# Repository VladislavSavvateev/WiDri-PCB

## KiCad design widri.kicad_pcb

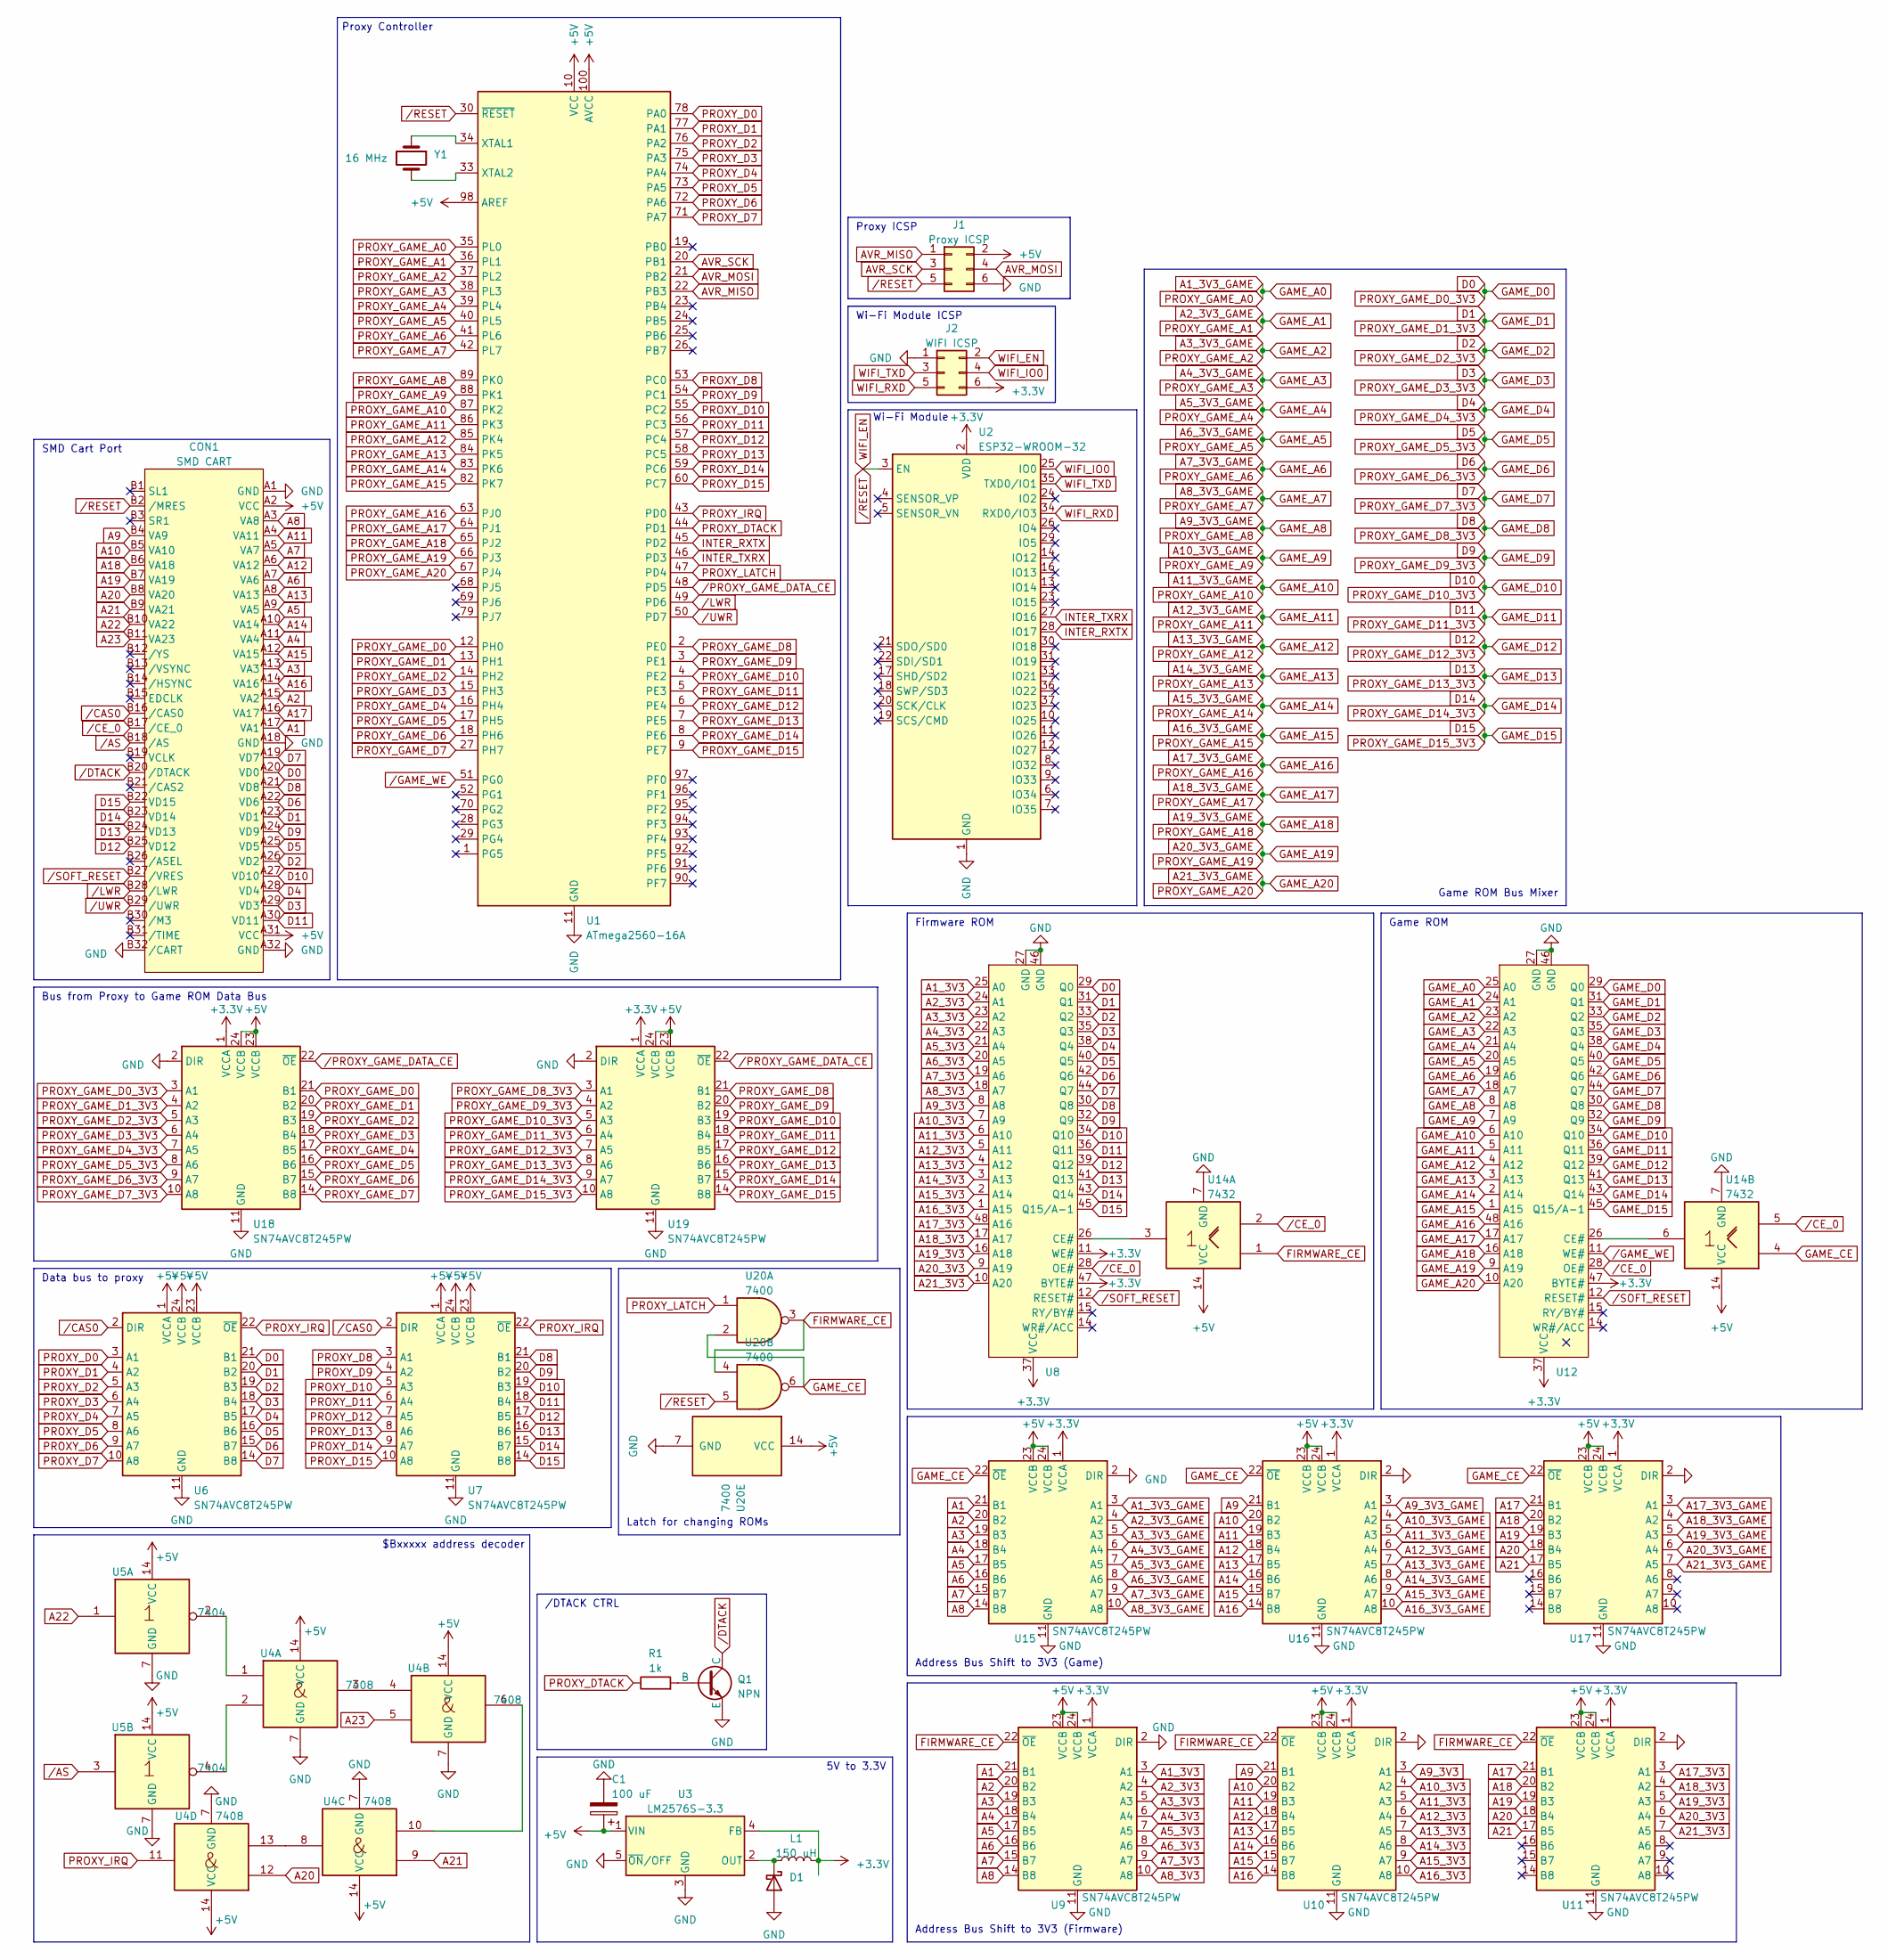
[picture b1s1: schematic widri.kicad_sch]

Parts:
C1: 100 uF; CP_Elec_6.3x5.4
CON1: SMD CART; SMD cart edge connector
D1: D_SMA
J1: Proxy ICSP; PinHeader_2x03_P2.54mm_Vertical
J2: WIFI ICSP; PinHeader_2x03_P2.54mm_Vertical
L1: 150 uH; L_1812_4532Metric
Q1: NPN; TSOP-6_1.65x3.05mm_P0.95mm
R1: 1k; R_1206_3216Metric
U1: ATmega2560-16A; TQFP-100_14x14mm_P0.5mm
U2: ESP32-WROOM-32
U3: LM2576S-3.3; TO-263-5_TabPin3
U4: 7408; SOIC-14_3.9x8.7mm_P1.27mm
U5: 7404; SOIC-14_3.9x8.7mm_P1.27mm
U6, U7, U9, U10, U11, U15, U16, U17, U18, U19: SN74AVC8T245PW; TSSOP-24_4.4x7.8mm_P0.65mm
U8, U12: TSOP-I-48_18.4x12mm_P0.5mm
U14: 7432; SOIC-14_3.9x8.7mm_P1.27mm
U20: 7400; SOIC-14_3.9x8.7mm_P1.27mm
Y1: 16 MHz; Crystal_HC49-U_Vertical

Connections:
+3.3V: J2.6, L1.2, U2.2 (VDD), U3.4 (FB), U8.11 (WE#), U8.37 (VCC), U8.47 (BYTE#), U9.1 (VCCA), U10.1 (VCCA), U11.1 (VCCA), U12.37 (VCC), U12.47 (BYTE#), U15.1 (VCCA), U16.1 (VCCA), U17.1 (VCCA), U18.1 (VCCA), U19.1 (VCCA)
+5V: C1.1, CON1.A2 (VCC), CON1.A31 (VCC), J1.2, U1.10 (VCC), U1.31 (VCC), U1.61 (VCC), U1.80 (VCC), U1.98 (AREF), U1.100 (AVCC), U3.1 (VIN), U4.14 (VCC), U5.14 (VCC), U6.1 (VCCA), U6.23 (VCCB), U6.24 (VCCB), U7.1 (VCCA), U7.23 (VCCB), U7.24 (VCCB), U9.23 (VCCB), U9.24 (VCCB), U10.23 (VCCB), U10.24 (VCCB), U11.23 (VCCB), U11.24 (VCCB), U14.14 (VCC), U15.23 (VCCB), U15.24 (VCCB), U16.23 (VCCB), U16.24 (VCCB), U17.23 (VCCB), U17.24 (VCCB), U18.23 (VCCB), U18.24 (VCCB), U19.23 (VCCB), U19.24 (VCCB), U20.14 (VCC)
A1: CON1.A17 (VA1), U9.21 (B1), U15.21 (B1)
A1_3V3: U8.25 (A0), U9.3 (A1)
A1_3V3_GAME: U1.35 (PL0), U12.25 (A0), U15.3 (A1)
A2: CON1.A15 (VA2), U9.20 (B2), U15.20 (B2)
A2_3V3: U8.24 (A1), U9.4 (A2)
A2_3V3_GAME: U1.36 (PL1), U12.24 (A1), U15.4 (A2)
A3: CON1.A13 (VA3), U9.19 (B3), U15.19 (B3)
A3_3V3: U8.23 (A2), U9.5 (A3)
A3_3V3_GAME: U1.37 (PL2), U12.23 (A2), U15.5 (A3)
A4: CON1.A11 (VA4), U9.18 (B4), U15.18 (B4)
A4_3V3: U8.22 (A3), U9.6 (A4)
A4_3V3_GAME: U1.38 (PL3), U12.22 (A3), U15.6 (A4)
A5: CON1.A9 (VA5), U9.17 (B5), U15.17 (B5)
A5_3V3: U8.21 (A4), U9.7 (A5)
A5_3V3_GAME: U1.39 (PL4), U12.21 (A4), U15.7 (A5)
A6: CON1.A7 (VA6), U9.16 (B6), U15.16 (B6)
A6_3V3: U8.20 (A5), U9.8 (A6)
A6_3V3_GAME: U1.40 (PL5), U12.20 (A5), U15.8 (A6)
A7: CON1.A5 (VA7), U9.15 (B7), U15.15 (B7)
A7_3V3: U8.19 (A6), U9.9 (A7)
A7_3V3_GAME: U1.41 (PL6), U12.19 (A6), U15.9 (A7)
A8: CON1.A3 (VA8), U9.14 (B8), U15.14 (B8)
A8_3V3: U8.18 (A7), U9.10 (A8)
A8_3V3_GAME: U1.42 (PL7), U12.18 (A7), U15.10 (A8)
A9: CON1.B4 (VA9), U10.21 (B1), U16.21 (B1)
A9_3V3: U8.8 (A8), U10.3 (A1)
A9_3V3_GAME: U1.89 (PK0), U12.8 (A8), U16.3 (A1)
A10: CON1.B5 (VA10), U10.20 (B2), U16.20 (B2)
A10_3V3: U8.7 (A9), U10.4 (A2)
A10_3V3_GAME: U1.88 (PK1), U12.7 (A9), U16.4 (A2)
A11: CON1.A4 (VA11), U10.19 (B3), U16.19 (B3)
A11_3V3: U8.6 (A10), U10.5 (A3)
A11_3V3_GAME: U1.87 (PK2), U12.6 (A10), U16.5 (A3)
A12: CON1.A6 (VA12), U10.18 (B4), U16.18 (B4)
A12_3V3: U8.5 (A11), U10.6 (A4)
A12_3V3_GAME: U1.86 (PK3), U12.5 (A11), U16.6 (A4)
A13: CON1.A8 (VA13), U10.17 (B5), U16.17 (B5)
A13_3V3: U8.4 (A12), U10.7 (A5)
A13_3V3_GAME: U1.85 (PK4), U12.4 (A12), U16.7 (A5)
A14: CON1.A10 (VA14), U10.16 (B6), U16.16 (B6)
A14_3V3: U8.3 (A13), U10.8 (A6)
A14_3V3_GAME: U1.84 (PK5), U12.3 (A13), U16.8 (A6)
A15: CON1.A12 (VA15), U10.15 (B7), U16.15 (B7)
A15_3V3: U8.2 (A14), U10.9 (A7)
A15_3V3_GAME: U1.83 (PK6), U12.2 (A14), U16.9 (A7)
A16: CON1.A14 (VA16), U10.14 (B8), U16.14 (B8)
A16_3V3: U8.1 (A15), U10.10 (A8)
A16_3V3_GAME: U1.82 (PK7), U12.1 (A15), U16.10 (A8)
A17: CON1.A16 (VA17), U11.21 (B1), U17.21 (B1)
A17_3V3: U8.48 (A16), U11.3 (A1)
A17_3V3_GAME: U1.63 (PJ0), U12.48 (A16), U17.3 (A1)
A18: CON1.B6 (VA18), U11.20 (B2), U17.20 (B2)
A18_3V3: U8.17 (A17), U11.4 (A2)
A18_3V3_GAME: U1.64 (PJ1), U12.17 (A17), U17.4 (A2)
A19: CON1.B7 (VA19), U11.19 (B3), U17.19 (B3)
A19_3V3: U8.16 (A18), U11.5 (A3)
A19_3V3_GAME: U1.65 (PJ2), U12.16 (A18), U17.5 (A3)
A20: CON1.B8 (VA20), U4.12, U11.18 (B4), U17.18 (B4)
A20_3V3: U8.9 (A19), U11.6 (A4)
A20_3V3_GAME: U1.66 (PJ3), U12.9 (A19), U17.6 (A4)
A21: CON1.B9 (VA21), U4.9, U11.17 (B5), U17.17 (B5)
A21_3V3: U8.10 (A20), U11.7 (A5)
A21_3V3_GAME: U1.67 (PJ4), U12.10 (A20), U17.7 (A5)
A22: CON1.B10 (VA22), U5.1
A23: CON1.B11 (VA23), U4.5
AVR_MISO: J1.1, U1.22 (PB3)
AVR_MOSI: J1.4, U1.21 (PB2)
AVR_SCK: J1.3, U1.20 (PB1)
D0: CON1.A20 (VD0), U6.21 (B1), U8.29 (Q0), U12.29 (Q0), U18.3 (A1)
D1: CON1.A23 (VD1), U6.20 (B2), U8.31 (Q1), U12.31 (Q1), U18.4 (A2)
D2: CON1.A26 (VD2), U6.19 (B3), U8.33 (Q2), U12.33 (Q2), U18.5 (A3)
D3: CON1.A29 (VD3), U6.18 (B4), U8.35 (Q3), U12.35 (Q3), U18.6 (A4)
D4: CON1.A28 (VD4), U6.17 (B5), U8.38 (Q4), U12.38 (Q4), U18.7 (A5)
D5: CON1.A25 (VD5), U6.16 (B6), U8.40 (Q5), U12.40 (Q5), U18.8 (A6)
D6: CON1.A22 (VD6), U6.15 (B7), U8.42 (Q6), U12.42 (Q6), U18.9 (A7)
D7: CON1.A19 (VD7), U6.14 (B8), U8.44 (Q7), U12.44 (Q7), U18.10 (A8)
D8: CON1.A21 (VD8), U7.21 (B1), U8.30 (Q8), U12.30 (Q8), U19.3 (A1)
D9: CON1.A24 (VD9), U7.20 (B2), U8.32 (Q9), U12.32 (Q9), U19.4 (A2)
D10: CON1.A27 (VD10), U7.19 (B3), U8.34 (Q10), U12.34 (Q10), U19.5 (A3)
D11: CON1.A30 (VD11), U7.18 (B4), U8.36 (Q11), U12.36 (Q11), U19.6 (A4)
D12: CON1.B25 (VD12), U7.17 (B5), U8.39 (Q12), U12.39 (Q12), U19.7 (A5)
D13: CON1.B24 (VD13), U7.16 (B6), U8.41 (Q13), U12.41 (Q13), U19.8 (A6)
D14: CON1.B23 (VD14), U7.15 (B7), U8.43 (Q14), U12.43 (Q14), U19.9 (A7)
D15: CON1.B22 (VD15), U7.14 (B8), U8.45 (Q15/A-1), U12.45 (Q15/A-1), U19.10 (A8)
FIRMWARE_CE: U9.22 (~OE), U10.22 (~OE), U11.22 (~OE), U14.1, U20.3, U20.4
GAME_CE: U14.4, U15.22 (~OE), U16.22 (~OE), U17.22 (~OE), U20.2, U20.6
GND: C1.2, CON1.A1 (GND), CON1.A18 (GND), CON1.A32 (GND), CON1.B32 (/CART), D1.2 (A), J1.6, J2.1, Q1.3 (E), U1.11 (GND), U1.32 (GND), U1.62 (GND), U1.81 (GND), U1.99 (GND), U2.1 (GND), U2.15 (GND), U2.38 (GND), U2.39 (GND), U3.3 (GND), U3.5 (~ON/OFF), U4.7 (GND), U5.7 (GND), U6.11 (GND), U6.12 (GND), U6.13 (GND), U7.11 (GND), U7.12 (GND), U7.13 (GND), U8.27 (GND), U8.46 (GND), U9.2 (DIR), U9.11 (GND), U9.12 (GND), U9.13 (GND), U10.2 (DIR), U10.11 (GND), U10.12 (GND), U10.13 (GND), U11.2 (DIR), U11.11 (GND), U11.12 (GND), U11.13 (GND), U12.27 (GND), U12.46 (GND), U14.7 (GND), U15.2 (DIR), U15.11 (GND), U15.12 (GND), U15.13 (GND), U16.2 (DIR), U16.11 (GND), U16.12 (GND), U16.13 (GND), U17.2 (DIR), U17.11 (GND), U17.12 (GND), U17.13 (GND), U18.2 (DIR), U18.11 (GND), U18.12 (GND), U18.13 (GND), U19.2 (DIR), U19.11 (GND), U19.12 (GND), U19.13 (GND), U20.7 (GND)
INTER_RXTX: U1.45 (PD2), U2.28 (IO17)
INTER_TXRX: U1.46 (PD3), U2.27 (IO16)
unnamed: D1.1 (K), L1.1, U3.2 (OUT)
unnamed: Q1.2 (B), R1.2
unnamed: U1.34 (XTAL1), Y1.1
unnamed: U1.33 (XTAL2), Y1.2
unnamed: U4.1, U5.2
unnamed: U4.2, U5.4
unnamed: U4.3, U4.4
unnamed: U4.6, U4.10
unnamed: U4.8, U4.13
unnamed: U8.26 (CE#), U14.3
unnamed: U12.26 (CE#), U14.6
PROXY_D0: U1.78 (PA0), U6.3 (A1)
PROXY_D1: U1.77 (PA1), U6.4 (A2)
PROXY_D2: U1.76 (PA2), U6.5 (A3)
PROXY_D3: U1.75 (PA3), U6.6 (A4)
PROXY_D4: U1.74 (PA4), U6.7 (A5)
PROXY_D5: U1.73 (PA5), U6.8 (A6)
PROXY_D6: U1.72 (PA6), U6.9 (A7)
PROXY_D7: U1.71 (PA7), U6.10 (A8)
PROXY_D8: U1.53 (PC0), U7.3 (A1)
PROXY_D9: U1.54 (PC1), U7.4 (A2)
PROXY_D10: U1.55 (PC2), U7.5 (A3)
PROXY_D11: U1.56 (PC3), U7.6 (A4)
PROXY_D12: U1.57 (PC4), U7.7 (A5)
PROXY_D13: U1.58 (PC5), U7.8 (A6)
PROXY_D14: U1.59 (PC6), U7.9 (A7)
PROXY_D15: U1.60 (PC7), U7.10 (A8)
PROXY_DTACK: R1.1, U1.44 (PD1)
PROXY_GAME_D0: U1.12 (PH0), U18.21 (B1)
PROXY_GAME_D1: U1.13 (PH1), U18.20 (B2)
PROXY_GAME_D2: U1.14 (PH2), U18.19 (B3)
PROXY_GAME_D3: U1.15 (PH3), U18.18 (B4)
PROXY_GAME_D4: U1.16 (PH4), U18.17 (B5)
PROXY_GAME_D5: U1.17 (PH5), U18.16 (B6)
PROXY_GAME_D6: U1.18 (PH6), U18.15 (B7)
PROXY_GAME_D7: U1.27 (PH7), U18.14 (B8)
PROXY_GAME_D8: U1.2 (PE0), U19.21 (B1)
PROXY_GAME_D9: U1.3 (PE1), U19.20 (B2)
PROXY_GAME_D10: U1.4 (PE2), U19.19 (B3)
PROXY_GAME_D11: U1.5 (PE3), U19.18 (B4)
PROXY_GAME_D12: U1.6 (PE4), U19.17 (B5)
PROXY_GAME_D13: U1.7 (PE5), U19.16 (B6)
PROXY_GAME_D14: U1.8 (PE6), U19.15 (B7)
PROXY_GAME_D15: U1.9 (PE7), U19.14 (B8)
PROXY_IRQ: U1.43 (PD0), U4.11, U6.22 (~OE), U7.22 (~OE)
PROXY_LATCH: U1.47 (PD4), U20.1
WIFI_EN: CON1.B2 (/MRES), J1.5, J2.2, U1.30 (~RESET), U2.3 (EN), U20.5
WIFI_IO0: J2.4, U2.25 (IO0)
WIFI_RXD: J2.5, U2.34 (RXD0/IO3)
WIFI_TXD: J2.3, U2.35 (TXD0/IO1)
/AS: CON1.B18 (/AS), U5.3
/CAS0: CON1.B16 (/CAS0), U6.2 (DIR), U7.2 (DIR)
/CE_0: CON1.B17 (/CE_0), U8.28 (OE#), U12.28 (OE#), U14.2, U14.5
/DTACK: CON1.B20 (/DTACK), Q1.1 (C)
/GAME_WE: U1.51 (PG0), U12.11 (WE#)
/LWR: CON1.B28 (/LWR), U1.49 (PD6)
/PROXY_GAME_DATA_CE: U1.48 (PD5), U18.22 (~OE), U19.22 (~OE)
/SOFT_RESET: CON1.B27 (/VRES), U8.12 (RESET#), U12.12 (RESET#)
/UWR: CON1.B29 (/UWR), U1.50 (PD7)

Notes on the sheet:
Proxy ICSP
Latch for changing ROMs
Address Bus Shift to 3V3 (Game)
Address Bus Shift to 3V3 (Firmware)
Bus from Proxy to Game ROM Data Bus
Proxy Controller
SMD Cart Port
5V to 3.3V
/DTACK CTRL
Wi-Fi Module ICSP
Firmware ROM
Game ROM
Game ROM Bus Mixer
Wi-Fi Module
Data bus to proxy
$Bxxxxx address decoder

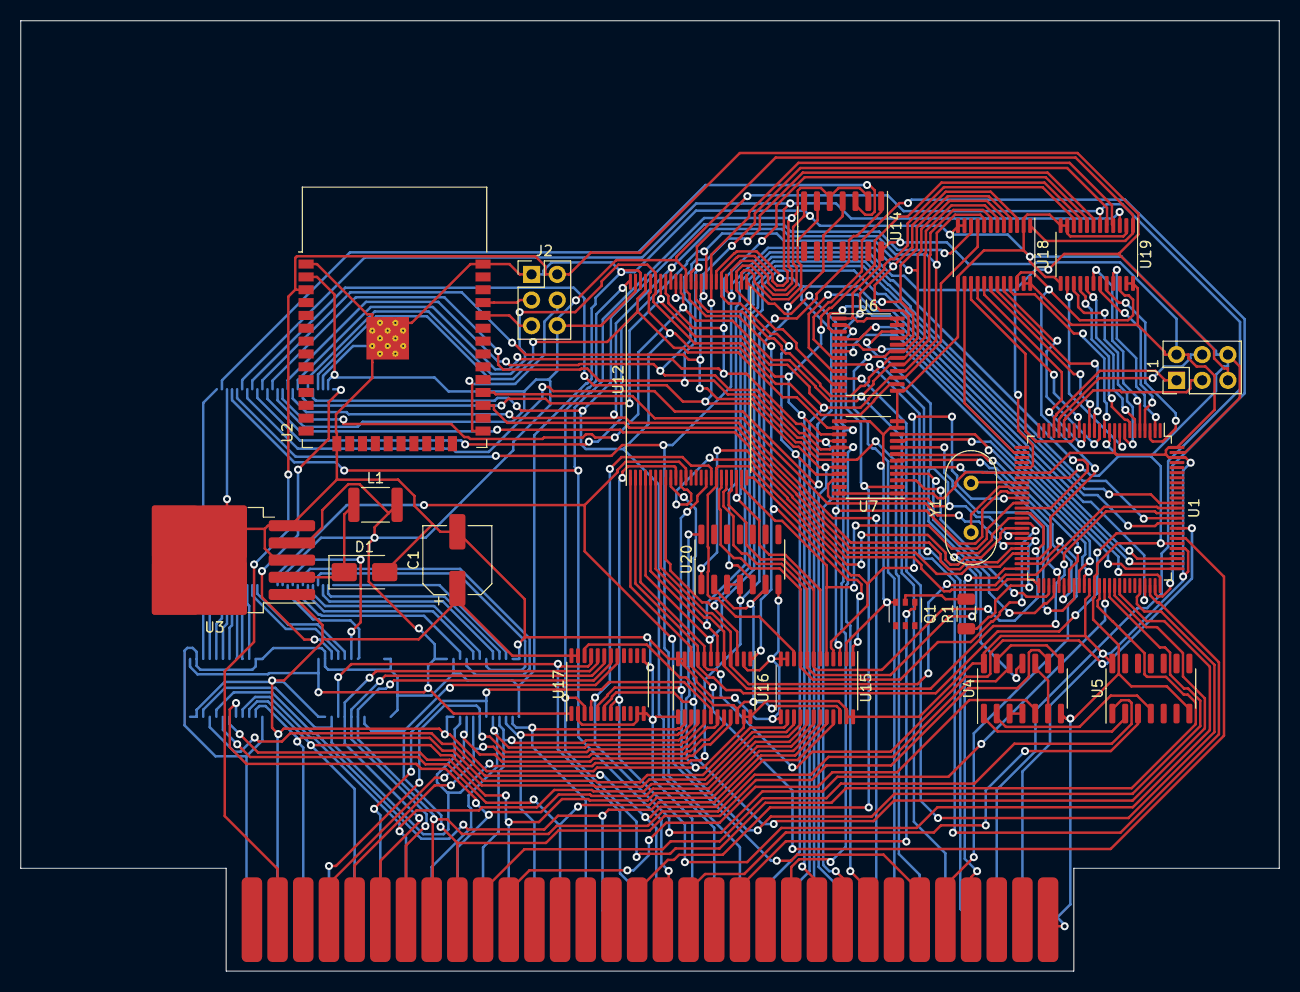
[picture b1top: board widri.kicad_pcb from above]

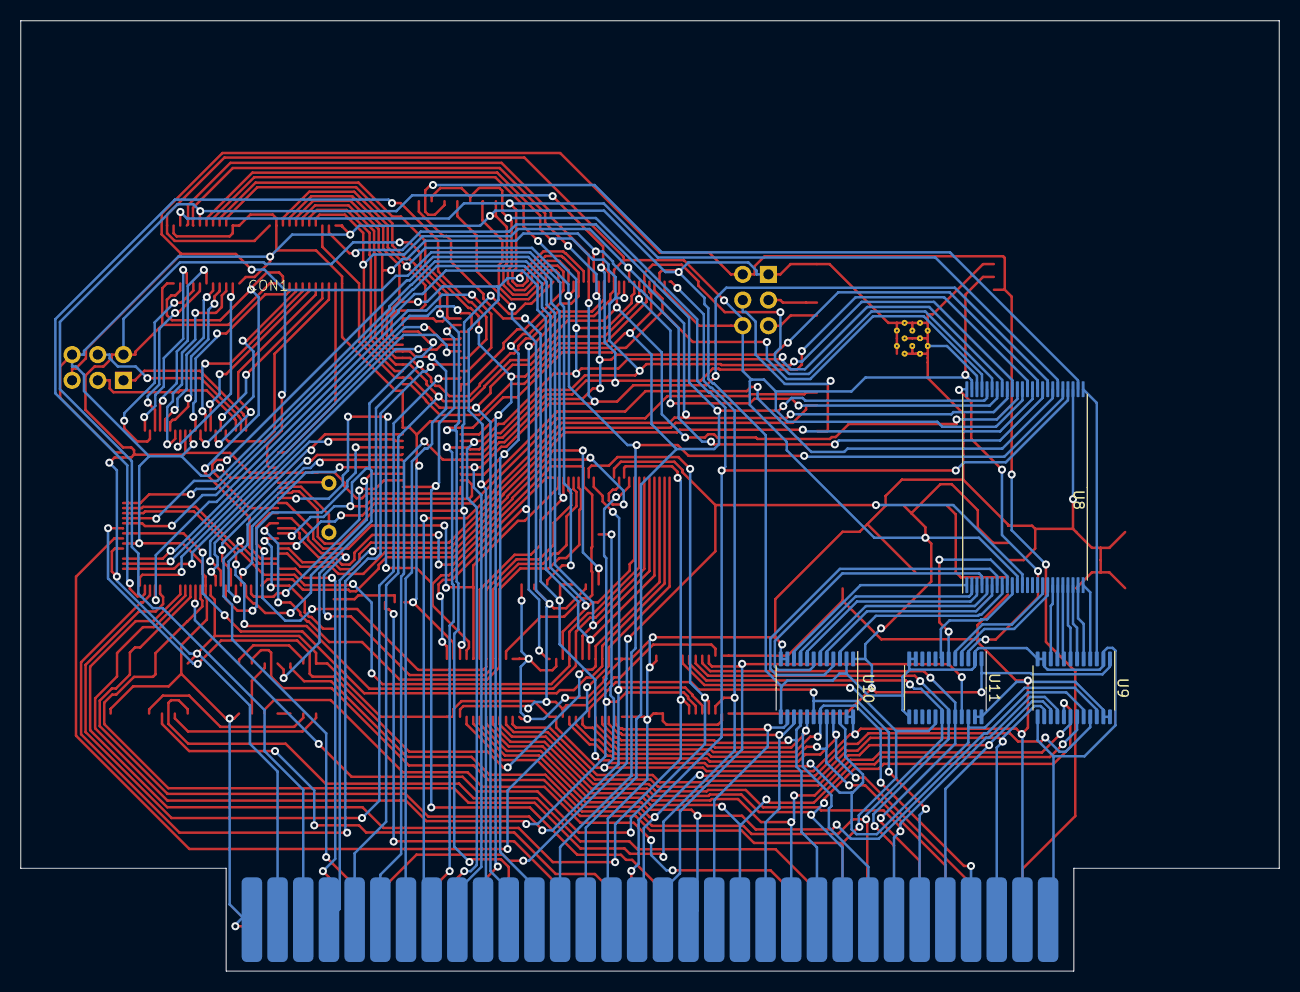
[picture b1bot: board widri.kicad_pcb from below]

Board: 2 copper layers, 124.5 x 94.0 mm, 28 parts (4 on the bottom side), 150 nets.
